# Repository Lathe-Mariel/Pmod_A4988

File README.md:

# Pmod_A4988
A4988 StepperMotor_Driver for Pmod

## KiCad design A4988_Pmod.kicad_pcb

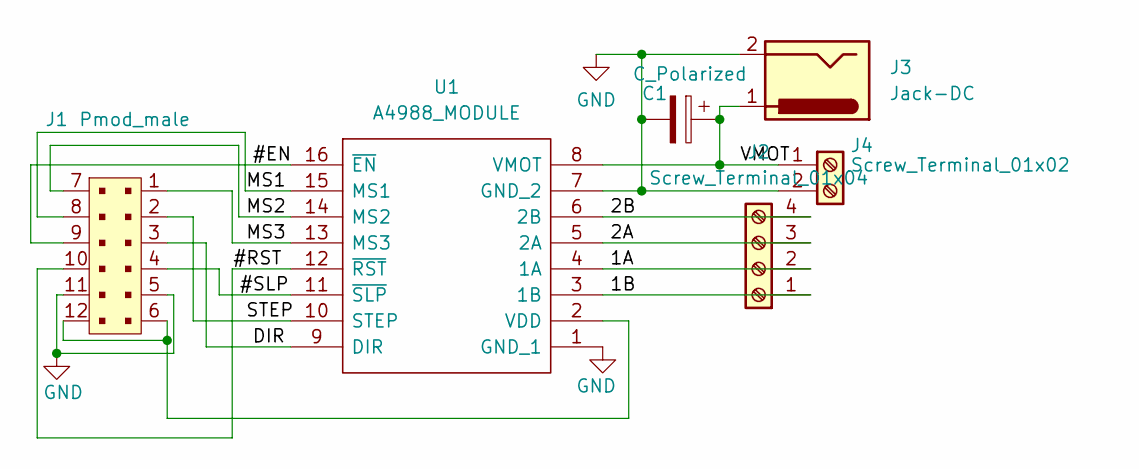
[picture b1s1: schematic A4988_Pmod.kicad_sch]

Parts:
C1: C_Polarized; CP_Radial_D5.0mm_P2.50mm
J1: Pmod_male; PinHeader_2x06_P2.54mm_Horizontal
J2: Screw_Terminal_01x04; TerminalBlock_bornier-4_P5.08mm
J3: Jack-DC; BarrelJack_Horizontal
J4: Screw_Terminal_01x02; TerminalBlock_bornier-2_P5.08mm
U1: A4988_MODULE; A4988MODULE; Manufacturer_Part_Number A4988 MODULE

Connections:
/1A: J2.2, U1.4 (1A)
/1B: J2.1, U1.3 (1B)
/2A: J2.3, U1.5 (2A)
/2B: J2.4, U1.6 (2B)
/#EN: J1.9, U1.16 (~EN)
/#RST: J1.10, U1.12 (~RST)
/#SLP: J1.4, U1.11 (~SLP)
/DIR: J1.3, U1.9 (DIR)
/MS1: J1.8, U1.15 (MS1)
/MS2: J1.7, U1.14 (MS2)
/MS3: J1.1, U1.13 (MS3)
/STEP: J1.2, U1.10 (STEP)
/VMOT: C1.1, J3.1, J4.1, U1.8 (VMOT)
GND: C1.2, J1.5, J1.11, J3.2, J3.3, J4.2, U1.1 (GND_1), U1.7 (GND_2)
unnamed: J1.6, J1.12, U1.2 (VDD)

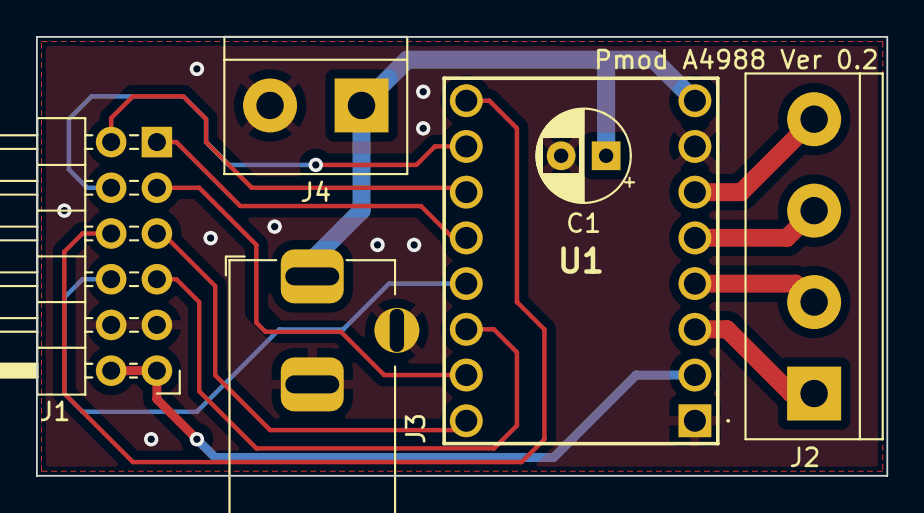
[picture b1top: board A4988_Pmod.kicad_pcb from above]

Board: 2 copper layers, 47.2 x 24.4 mm, 6 parts (0 on the bottom side), 15 nets.
